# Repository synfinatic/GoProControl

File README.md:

# GoProControl

## About

I wanted an easy way to syncronize my GoPro videos with the data generated from
my data logger.  In the past, I've done this manually with
[DashWare](http://www.dashware.net), but it is a tedious manual process to get
them syncronized.  There had to be a better way!

I realized that many GoPro's (GoPro3 Silver/Black, GoPro4, etc) have built in
WiFi and we all know about the iPhone and Android apps.  So clearly there was a
way to controll them via WiFi.

GoProControl is a simple box you can plug into your car or motorcycle and
connect to your datalogger's digital output or input sensor.  I use the
inexpensive [ESP8266](http://www.esp8266.com/) to control the a GoPro.  In the
future, I hope to be able to control multiple GoPro's like the [GoPro
Remote](http://shop.gopro.com/accessories/smart-remote/ARMTE-002.html) can.

## How it works

GoProControl has 4 pins:

 1. +5-12V
 2. GND
 3. Digital Input 
 4. Digital Ouput
 
When GoProControl is turned on, it will send a signal to the GoPro to also turn
on- which may take a few seconds.  When the Digital Input is connected to
ground (GND) it will tell the GoPro to start recording. 

When the Digital Input is disconnected from ground (floating or +3.3-12V) it
will tell the GoPro to stop recording.  You should configure your GoPro to
auto-off after 60seconds to save battery.

Note, when the Digital Input is connected to ground, the Digital Output will be
driven to 3.3V.  This is so if your data logger does not have an output channel
you can control, you can use a simple toggle switch to both turn on the GoPro
and mark the time when recording started in your data logger using an input
channel on your data logger.

**Note:** If you have the option of powering this by 5 or 12V, use 5V.  If
using your vehicle's battery, be sure it is switched with the ignition to
prevent draining your battery as this circuit uses ~330mA.

## Programming

The GoProControl board has an onboard connector for programming via a FTDI
cable.  This cable should provide 5V of power and can use either 3.3V or 
5V for signalling.

Configure your GoPro WiFi for "App Mode" and define a SSID and WiFi Password.

Before programming your GoProController, you first need to edit 
**src/goprocontrol/goprocontrol.ino** and edit the SSID and WIFI_PASSWORD
to match your GoPro's settings.

In order to program your GoProController, you will need to start the Arduino
application and figure out what serial speed (baud) your ESP8266 communicates
at.  Older boards run at 9600, while newer boards seem to run at 115200.  

Once you have figured out the serial speed, configure Arduino for a 
"Generic ESP8266 Module" and the upload speed to the same speed.  Then, 
with the board powered up:

 1. Press and hold the PROG button
 2. Press and release the RST button
 3. Release the PROG button
 4. Uplaod the sketch via the Arduino application

## Links Links to projects or information that was critical to me creating this
project.  Thank you!

 * [GoProWiFiHack](https://github.com/KonradIT/goprowifihack)
 * [GoProController](https://github.com/joshvillbrandt/GoProController)
 * [GoProHero](https://github.com/joshvillbrandt/goprohero)
 * [GoProControllerUI](https://github.com/joshvillbrandt/GoProControllerUI)

## License

GoProControl is GPLv3

## Trademarks

GoPro, GoPro3 and GoPro4 are trademark [GoPro](http://www.gopro.com).

GoProControl is not affiliated with GoPro in any way.

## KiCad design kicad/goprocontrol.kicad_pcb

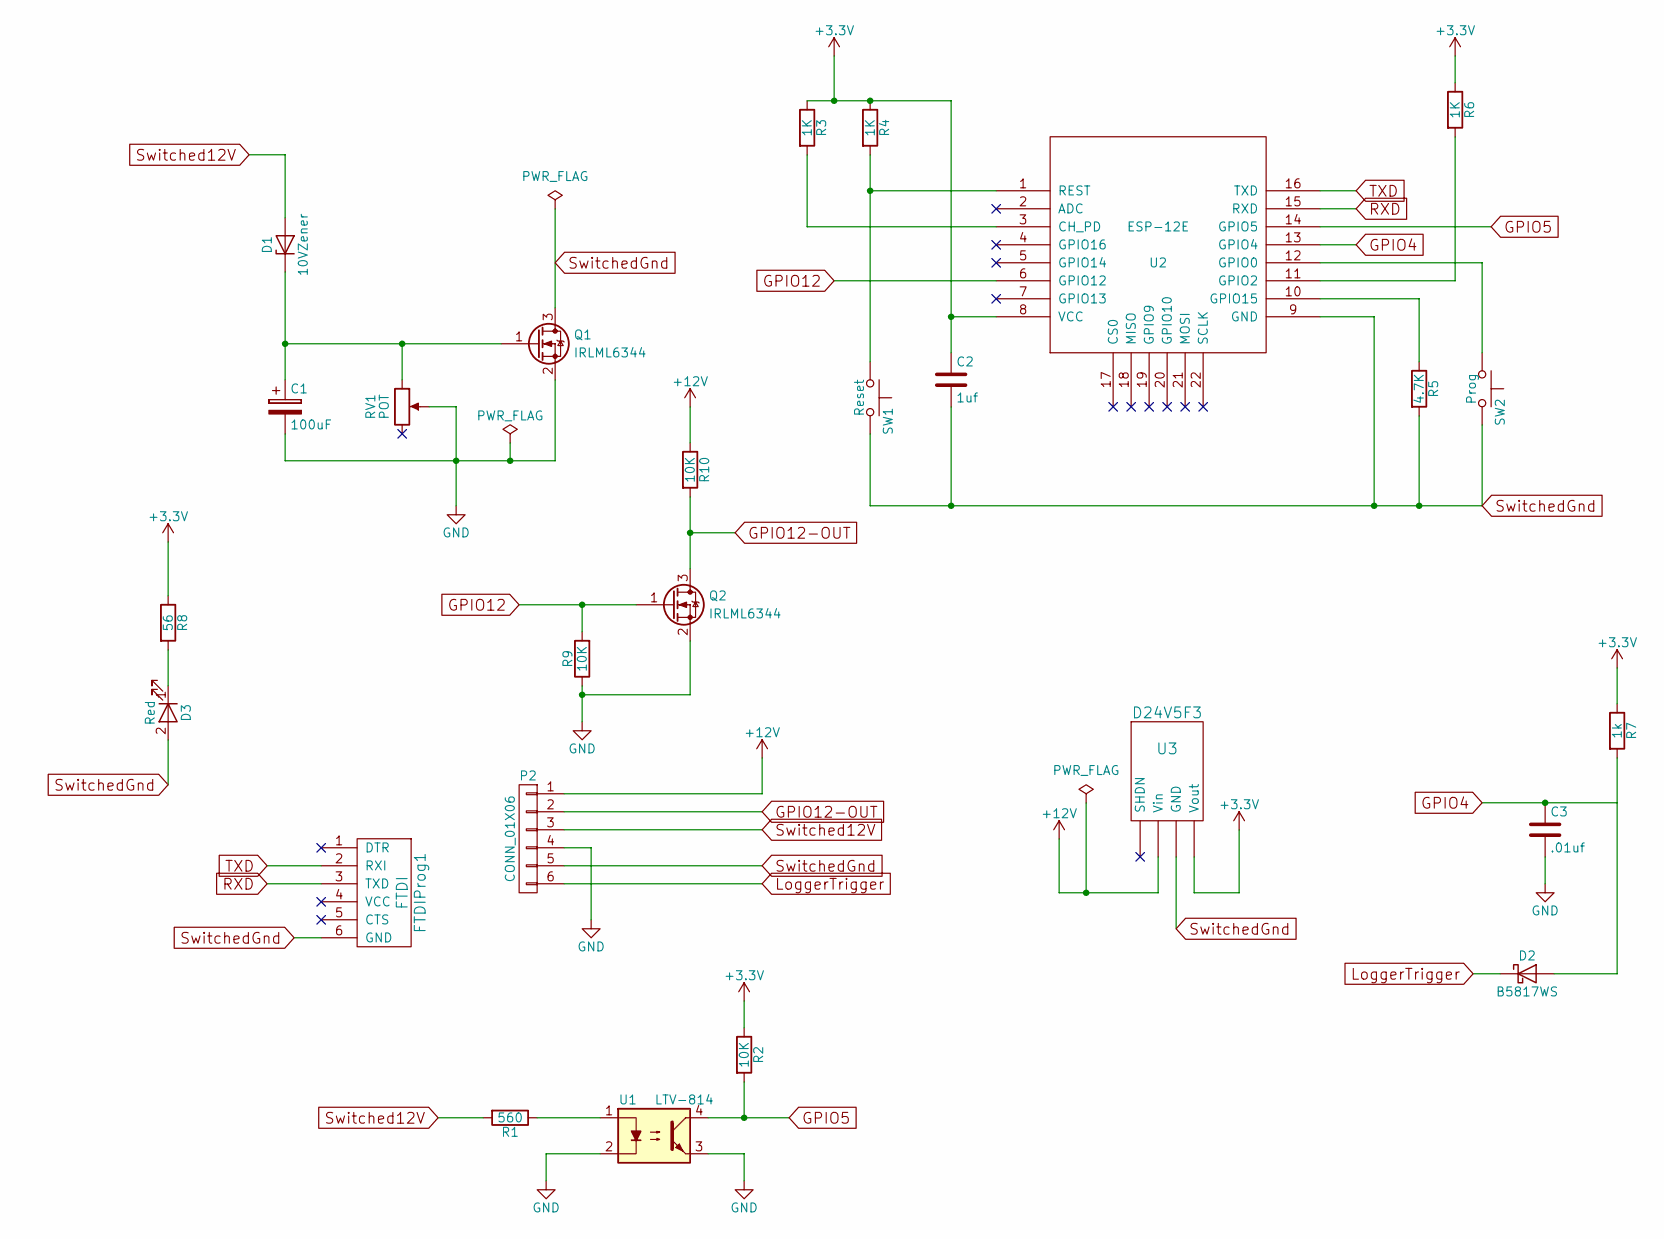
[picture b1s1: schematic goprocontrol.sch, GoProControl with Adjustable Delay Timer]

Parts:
C1: 100uF; CP_Elec_6.3x7.7
C2: 1uf; C_0805_HandSoldering
C3: .01uf; C_0805_HandSoldering
D1: 10VZener; D_SOD-123F
D2: B5817WS; SOD-323_HandSoldering
D3: Red; LED_0805_HandSoldering
FTDIProg1: FTDI; FTDIHeader
P2: CONN_01X06; PhoenixContact_MSTBA-G_06x5.08mm_Angled
Q1, Q2: IRLML6344; SOT-23_Handsoldering
R1: 560; R_0805_HandSoldering
R2, R9, R10: 10K; R_0805_HandSoldering
R3, R4, R6: 1K; R_0805_HandSoldering
R5: 4.7K; R_0805_HandSoldering
R7: 1k; R_0805_HandSoldering
R8: 56; R_0805_HandSoldering
RV1: POT; Potentiometer_Bourns_3296W_3-8Zoll_Inline_ScrewUp
SW1: Reset; SPST-SMD-6x3.5
SW2: Prog; SPST-SMD-6x3.5
U1: LTV-814; Optocoupler_SMD_LTV-817S
U2: ESP-12E; ESP-12E-SMD
U3: D24V5F3; D24V5Fx

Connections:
+3V3: C2.1, R2.1, R3.1, R4.1, R6.1, R7.1, R8.1, U2.8 (VCC), U3.4 (Vout)
+12V: P2.1, R10.1, U3.2 (Vin)
GND: C1.2, C3.2, P2.4, Q1.2 (S), Q2.2 (S), R9.1, RV1.2, U1.2, U1.3
GPIO4: C3.1, U2.13 (GPIO4)
GPIO5: R2.2, U1.4, U2.14 (GPIO5)
GPIO12: Q2.1 (G), R9.2, U2.6 (GPIO12)
GPIO12-OUT: P2.2, Q2.3 (D), R10.2
LoggerTrigger: D2.1 (K), P2.6
unnamed: C1.1, D1.1 (K), Q1.1 (G), RV1.1
unnamed: D2.2 (A), R7.2
unnamed: D3.1 (K), R8.2
unnamed: R1.1, U1.1
unnamed: R3.2, U2.3 (CH_PD)
unnamed: R4.2, SW1.1, U2.1 (REST)
unnamed: R5.1, U2.10 (GPIO15)
unnamed: R6.2, U2.11 (GPIO2)
unnamed: SW2.1, U2.12 (GPIO0)
RXD: FTDIProg1.3 (TXD), U2.15 (RXD)
Switched12V: D1.2 (A), P2.3, R1.2
SwitchedGnd: C2.2, D3.2 (A), FTDIProg1.6 (GND), P2.5, Q1.3 (D), R5.2, SW1.2, SW2.2, U2.9 (GND), U3.3 (GND)
TXD: FTDIProg1.2 (RXI), U2.16 (TXD)

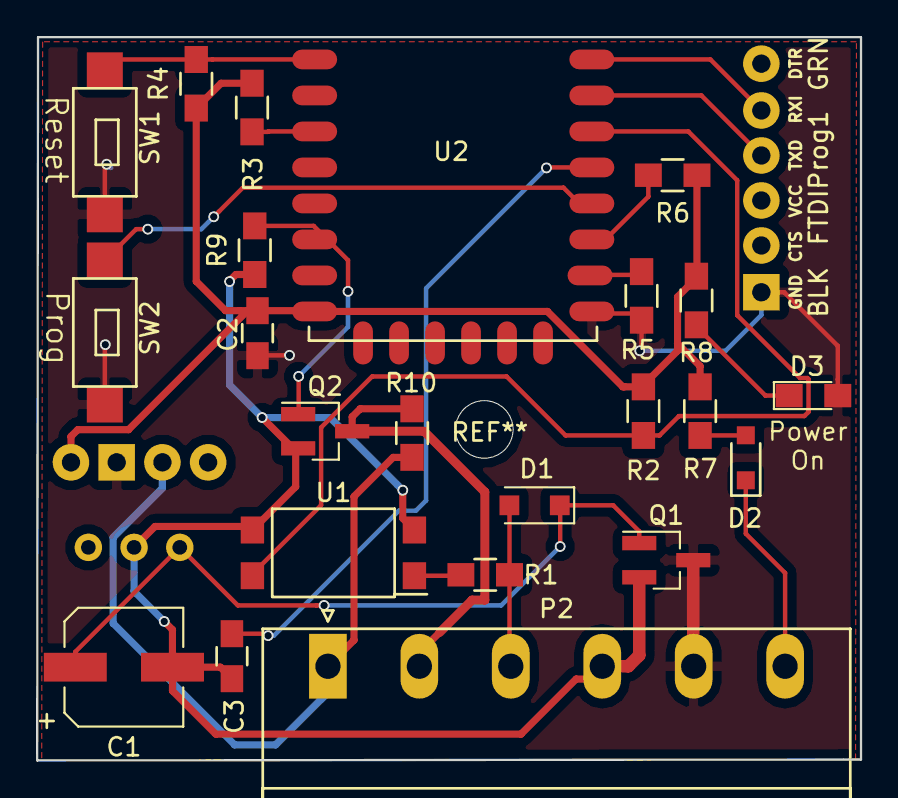
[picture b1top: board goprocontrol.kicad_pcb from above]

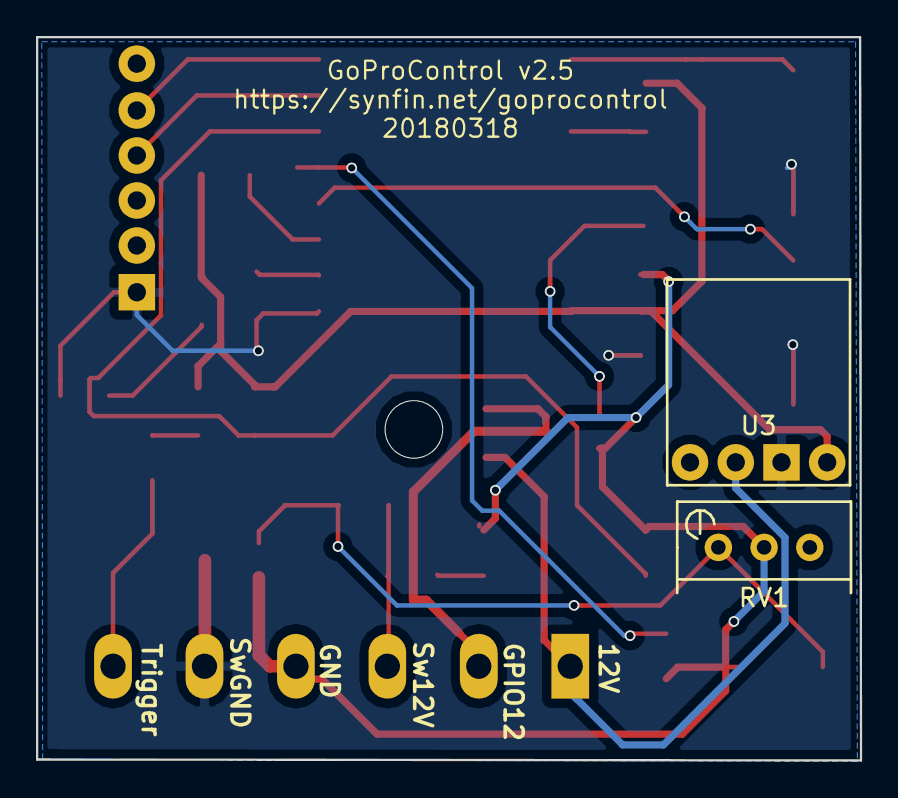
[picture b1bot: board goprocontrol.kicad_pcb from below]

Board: 2 copper layers, 45.8 x 40.2 mm, 26 parts (2 on the bottom side), 21 nets.

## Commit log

2015-12-06 initial commit. Basic board design, but want to change it
2015-12-06 update board to fit in sv650 ecu decoder box
2015-12-06 added ground planes top & bottom
2015-12-06 v0.1 release
    Fixed outline for term block and labled pins
2015-12-06 v0.2 small tweaks
    - trim board to better fit case
    - verify all DRC/ERC
2015-12-06 Better describe out circuit works
2015-12-06 v0.3
    - heat sink vias are now 0.35mm and have no exposed copper
    - 2x the number of heat sink vias
    - improved labels
2015-12-06 v0.4 fix diode pads
    My old sod-323 and sod-123 pads always seemed a bit wrong/too small
    these new pads are better.
2015-12-07 Helper program to play with ESP8266 using a Teensy 3.x
    Ok, this is lame, but none of my ESP8266 will talk via the
    FTDI cable I have so I ended up using an old Teensy 3.0 I had laying
    around to do the USB->Serial 3.3V converstion. It's lame, but it works.
2015-12-16 Add a 500ma PTC fuse to protect things
2015-12-16 Add pullup on GPIO0 for better reliability and switch to 10K pullups
2015-12-16 small cleanup to .sch
2015-12-16 First pass at some code:
    - Tries to connect to the GoPro WiFi AP
    - Tries to turn on the GoPro
    - When GPIO2 goes low, we start recording
    - When GPIO2 goes high, we stop recording
    Totally untested right now because I seem to be missing the compiler.
    :-/
2015-12-16 Fix & clean up the header file
    Don't need to build our own headers- the HTTP library does that
    Need to rewrite the requests
2015-12-17 Code compiles with ESP8266 v2.0.0 library
2015-12-18 Update PCB to v0.5
    - Switch to using more common 5V FTDI (VCC & signal)
    - Use Schottky diodes to protect reverse polarity and
    to make sure we don't send 12V onto the FTDI VCC line
    - Add 1uF cap to VCC on ESP8266 to stabilize things
    Still would be a good idea to protect against the FTDI
    cable being inserted backwards and putting 5V onto RXD
2015-12-30 Update PCB to v0.6
    - Replace LDO with a switching module
    - Update readme file
2016-01-23 Update board to v0.7
    - Fixes FTDI RX/TX reversal
    - Fixes GPIO2 pullup
    - Rotated termblock
    - Still needs to fix term block part to match
2016-01-24 v0.8 - ordered!
    - Tweaked footprints & labels
    - Changed term block outline to match OST TE 3.5mm
    - Added parts list
2016-03-03 Update code to work better (kinda)
    Code looks like it should work, but it crashes???
2016-03-03 Update PCB to v0.9
    - Just changed silk screen to swap Input/Output labels to
    match the actual pins!
2016-05-24 small board tweaks
2016-06-21 Basic working code
    Seems to work, but board needs to be modified to support
    a automatic shutdown
2016-10-08 renderings of v0.5 of the board
2017-02-26 Redesign board with KiCad
    Utilize 555 timer to do a delayed power off
    for the circuit and the data logger. Removes
    the output signal.
2017-03-12 Design new v2.0 board
    Still ESP8266 based
    Add delaytimer v1.1 circuit for power control
2017-03-12 update BOM
2017-10-15 GoProControl v2.1 ordered
2018-02-18 Rev board to v2.2
    - Switch to using ESP12E
    - Switch to using OptoIsolator + ESP power off detection
    - Using Pot to control power off delay
2018-03-11 v2.3 Board
    - Larger holes for 1x6 connector
    - Move 3.3V regulator out of the way
    - clean up traces
    - remove 3.3V FTDI selector
    - Move Prog switch
    - Better GND/SW-GND for MOSFET
2018-03-24 v2.5 of the board
    - Move main connector to front
    - Use MOSFET to drive GPIO12 like MXL2
    - Larger traces for Switched Ground

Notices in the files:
parts and their libraries:
SparkFun-Aesthetics: Licensing: Creative Commons ShareAlike 4.0 International - https://creativecommons.org/licenses/by-sa/4.0
SparkFun: Licensing: CC v3.0 Share-Alike You are welcome to use this library for commercial purposes.
